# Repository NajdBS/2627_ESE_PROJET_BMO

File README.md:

# 2627_ESE_PROJET_BMO
# Robot BMO - Ramasseur de Canettes
Projet d'Option 3A ESE (2026-2027)

## Objectif

Concevoir un robot **entièrement autonome** qui ramasse des canettes rouges et vertes posées en vrac au centre d'un terrain, puis range chacune dans la zone de sa couleur, sans aucune intervention humaine.

## Mission du robot

1. Trouver une canette dans la zone centrale.
2. S'en approcher et la saisir.
3. Identifier sa couleur.
4. La déposer dans la bonne zone sans renverser les canettes déjà déposées.
5. Ressortir de la zone et revenir au centre.
6. Ne jamais reprendre une canette qui se trouve déjà dans une zone verte ou rouge.
7. Recommencer jusqu'à ce que la zone centrale soit vide, puis s'arrêter.
## Équipe
- Najd BEN SAAD
- Yassin GARAFI
- Achraf AHAL

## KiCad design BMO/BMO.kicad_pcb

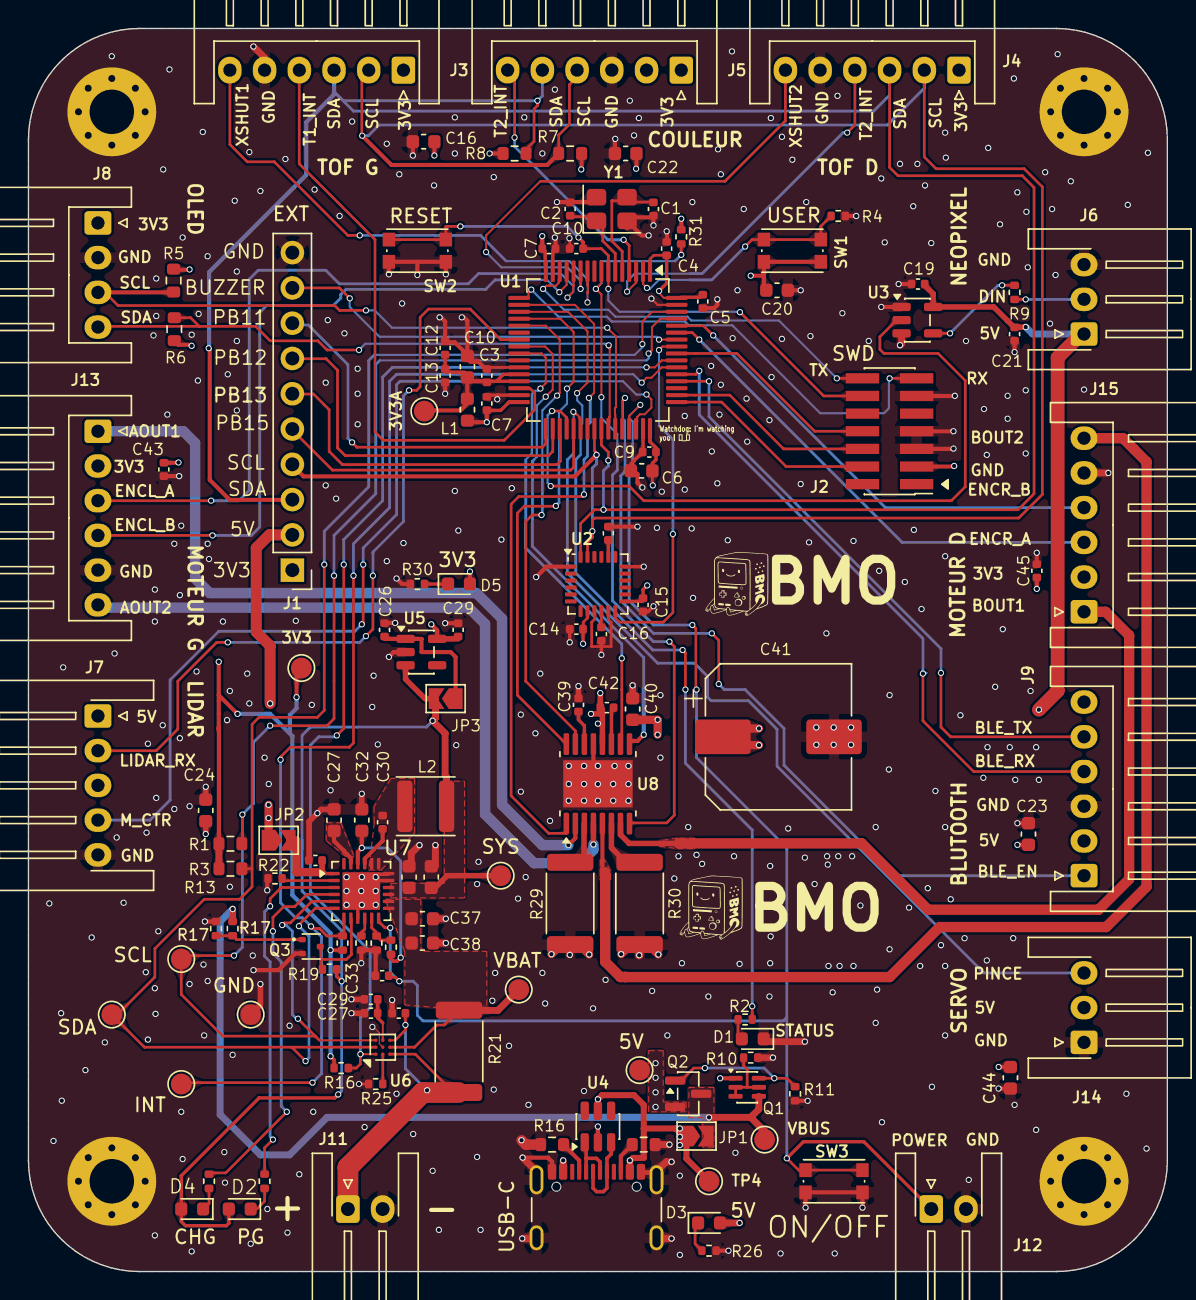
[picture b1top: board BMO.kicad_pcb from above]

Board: 4 copper layers, 82.0 x 89.5 mm, 131 parts (0 on the bottom side), 94 nets.

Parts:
3V3, 3V3A, 5V: TestPoint; TestPoint_Pad_D1.5mm
C1, C2: 10p; C_0402_1005Metric
C3, C4, C5, C7, C8, C9, C11, C15, C17, C19, C21, C34, C43, C45: 100n; C_0402_1005Metric
C6, C32: 4u7; C_0603_1608Metric
C10: 10n; C_0603_1608Metric
C12, C13, C25, C26, C30, C33: 1u; C_0402_1005Metric
C14, C42: 10n; C_0402_1005Metric
C16, C20, C22, C23, C24: 1u; C_0603_1608Metric
C18: 2n2/50V; C_0402_1005Metric
C27, C35, C36, C37, C38, C40, C44: 10u; C_0603_1608Metric
C28: 470n; C_0402_1005Metric
C29, C39: 2u2; C_0402_1005Metric
C31: 47n; C_0402_1005Metric
C41: 470u; CP_Elec_10x10
D1, D2: GREEN; LED_0603_1608Metric
D3: RED_5V; LED_0603_1608Metric
D4: ORANGE; LED_0603_1608Metric
D5: RED_3V; LED_0603_1608Metric
H1, H2, H3, H4: MountingHole_Pad; MountingHole_3.2mm_M3_Pad_Via
J1: EXT; PinHeader_1x10_P2.54mm_Vertical
J2: Conn_ST_STDC14; PinHeader_2x07_P1.27mm_Vertical_SMD
J3: TOF1_VL53L0X; JST_XH_S6B-XH-A_1x06_P2.50mm_Horizontal
J4: TOF2_VL53L0X; JST_XH_S6B-XH-A_1x06_P2.50mm_Horizontal
J5: COULEUR_I2C; JST_XH_S6B-XH-A_1x06_P2.50mm_Horizontal
J6: NEOPIXEL; JST_XH_S3B-XH-A-1_1x03_P2.50mm_Horizontal
J7: LIDAR_X2; JST_XH_S5B-XH-A-1_1x05_P2.50mm_Horizontal
J8: OLED_I2C; JST_XH_S4B-XH-A_1x04_P2.50mm_Horizontal
J9, J13, J15: Conn_01x06; JST_XH_S6B-XH-A_1x06_P2.50mm_Horizontal
J10: USB_C_Receptacle_USB2.0_16P; USB_C_Receptacle_GCT_USB4105-xx-A_16P_TopMnt_Horizontal
J11: BAT; JST_XH_S2B-XH-A-1_1x02_P2.50mm_Horizontal
J12: ON/OFF; JST_XH_S2B-XH-A-1_1x02_P2.50mm_Horizontal
J14: SERVO; JST_XH_S3B-XH-A-1_1x03_P2.50mm_Horizontal
JP1, JP2, JP3: SolderJumper_2_Open; SolderJumper-2_P1.3mm_Open_TrianglePad1.0x1.5mm
L1: 600R@100MHz; L_0603_1608Metric
L2: 1u; L_APV_ANR4020
Q1: MMDT2907A-7-F; SOT-363_SC-70-6
Q2: DMP1045U-7; SOT-23
Q3: DMN313DLT-7; SOT-523
R1, R3: 4k7; R_0603_1608Metric
R2, R26, R28: 1k; R_0402_1005Metric
R4, R16, R17, R19, R20, R22, R23, R24, R31: 10k; R_0402_1005Metric
R5, R6, R7, R8: 2k2; R_0603_1608Metric
R9: 330; R_0402_1005Metric
R10, R11: 100k; R_0402_1005Metric
R12: 4k7; R_0402_1005Metric
R13, R14: 5.1k; R_0603_1608Metric
R15: 100; R_0402_1005Metric
R18: 470; R_0402_1005Metric
R21: 10m; R_2512_6332Metric
R25, R27: 2k2; R_0402_1005Metric
R29, R30: 200m; R_2512_6332Metric
SW1: USER; SW_Push_1P1T_NO_CK_KMR2
SW2: SW_Push; SW_Push_1P1T_NO_CK_KMR2
SW3: nQON; SW_Push_1P1T_NO_CK_KMR2
SYS: TestPoint; TestPoint_Pad_D1.5mm
TP1, TP2, TP3, TP4, TP5: TestPoint; TestPoint_Pad_D1.5mm
U1: STM32G474RBTx; LQFP-64_10x10mm_P0.5mm
U2: MPU-6050; InvenSense_QFN-24_4x4mm_P0.5mm
U3: SN74AHCT1G125DBVR; SOT-23-5
U4: USBLC6-2SC6; SOT-23-6
U5: AP2112K-3.3; SOT-23-5
U6: BQ27220YZFR; Texas_DSBGA-9_1.62x1.58mm_Layout3x3_P0.5mm
U7: BQ25896RTW; Texas_RTW_WQFN-24-1EP_4x4mm_P0.5mm_EP2.7x2.7mm_ThermalVias
U8: DRV8833PWPR; HTSSOP-16-1EP_4.4x5mm_P0.65mm_EP3.4x5mm_Mask2.46x2.31mm_The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
VBAT: TestPoint; TestPoint_Pad_D1.5mm
VBUS: TestPoint; TestPoint_Pad_D1.5mm
Y1: 16MHz; Crystal_SMD_3225-4Pin_3.2x2.5mm

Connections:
+3.3V: 3V3.1 (1_1), C4.2, C5.2, C6.2, C7.2, C8.2, C9.2, C14.1, C15.1, C16.1, C20.1, C22.1, C30.1, C43.1, C45.1, D5.2 (A), J1.1, J2.3 (VCC), J3.1, J4.1, J5.1, J8.1, J13.2, J15.2, L1.1, R1.1, R3.1, R5.2, R6.2, R7.1, R8.1, R12.1, R16.2, R31.1, SW1.1, U1.1 (VBAT), U1.16 (VDD), U1.32 (VDD), U1.48 (VDD), U1.64 (VDD), U2.8 (VLOGIC), U2.13 (VDD), U5.5 (VOUT)
+5V: 5V.1 (1_1), C19.1, C21.2, C23.1, C24.1, C40.1, C41.1, C42.2, C44.1, D3.2 (A), J1.2, J6.1, J7.1, J9.2, J14.2, JP2.1 (A), Q1.1 (E1), Q2.2 (S), U3.5 (VCC), U8.12 (VM)
/Motors/ENC_L_A_TIM2_CH1: J13.3, U1.12 (PA0)
/Motors/ENC_L_B_TIM2_CH2: J13.4, U1.13 (PA1)
/Motors/ENC_R_A_TIM4_CH1: J15.3, U1.59 (PB6)
/Motors/ENC_R_B_TIM4_CH2: J15.4, U1.60 (PB7)
/Motors/MOT_L_IN1_TIM3_CH1: U1.20 (PA6), U8.16 (AIN1)
/Motors/MOT_L_IN2_TIM3_CH2: U1.21 (PA7), U8.15 (AIN2)
/Motors/MOT_R_IN1_TIM3_CH3: U1.24 (PB0), U8.9 (BIN1)
/Motors/MOT_R_IN2_TIM3_CH4: U1.25 (PB1), U8.10 (BIN2)
/Motors/SERVO_PINCE_TIM8_CH1: J14.3, U1.38 (PC6)
/Motors/VCP: C42.1, U8.11 (VCP)
/Motors/~FAULT: R31.2, U1.8 (PC0), U8.8 (~FAULT)
/Motors/~SLEEP: U1.18 (PA4), U8.1 (~SLEEP)
/Power/BAT: C37.1, C38.1, R21.1, U6.C2 (SRN), U7.13 (BAT), U7.14 (BAT), VBAT.1 (1_1)
/Power/CHARGER_INT: R12.2, TP3.1 (1_1), U1.54 (PC12), U7.7 (INT)
/Power/FG_GPOUT: R16.1, U1.55 (PD2), U6.A1 (GPOUT)
/Power/PWR_Bouton: C34.2, J12.1, SW3.1, U1.45 (PA11), U7.12 (~QON)
/Power/REGN: C32.1, R24.2, U7.22 (REGN)
/Power/STAT: R27.2, U7.4 (STAT)
/Power/USB_D+: J10.A6 (D+), J10.B6 (D+), U4.3 (I/O2)
/Power/USB_D-: J10.A7 (D-), J10.B7 (D-), U4.1 (I/O1)
/Power/~PG: R25.2, U7.3 (~PG)
/STM32G474RBT3/+3V3A: 3V3A.1 (1_1), C3.2, C10.2, C12.1, C13.1, L1.2, U1.28 (VREF+), U1.29 (VDDA)
/STM32G474RBT3/BLE_En: J9.1, U1.44 (PA10)
/STM32G474RBT3/BLE_USART3_RX: J9.4, U1.53 (PC11)
/STM32G474RBT3/BLE_USART3_TX: J9.5, U1.52 (PC10)
/STM32G474RBT3/BUZZER_TIM17_CH1: J1.9, U1.58 (PB5)
/STM32G474RBT3/COLOR_INT: J5.6, U1.4 (PC15)
/STM32G474RBT3/EXT_PB11: J1.8, U1.33 (PB11)
/STM32G474RBT3/EXT_PB12: J1.7, U1.34 (PB12)
/STM32G474RBT3/EXT_PB13: J1.6, U1.35 (PB13)
/STM32G474RBT3/EXT_PB15: J1.5, U1.37 (PB15)
/STM32G474RBT3/I2C1_SCL_Jauge: R1.2, TP2.1 (1_1), U1.61 (PB8), U6.A3 (SCL), U7.5 (SCL)
/STM32G474RBT3/I2C1_SDA_Jauge: R3.2, TP5.1 (1_1), U1.62 (PB9), U6.A2 (SDA), U7.6 (SDA)
/STM32G474RBT3/I2C2_SCL_OLED: J8.3, R5.1, U1.43 (PA9)
/STM32G474RBT3/I2C2_SDA_OLED: J8.4, R6.1, U1.42 (PA8)
/STM32G474RBT3/I2C3_SCL_ToF_TCS_MPU: J1.4, J3.2, J4.2, J5.4, R7.2, U1.40 (PC8), U2.23 (SCL)
/STM32G474RBT3/I2C3_SDA_ToF_TCS_MPU: J1.3, J3.3, J4.3, J5.5, R8.2, U1.41 (PC9), U2.24 (SDA)
/STM32G474RBT3/LED_STATUS: R2.1, U1.19 (PA5)
/STM32G474RBT3/LIDARX2__USART1_RX: J7.2, U1.23 (PC5)
/STM32G474RBT3/LIDAR_M_CTR_TIM16_CH1: J7.4, U1.46 (PA12)
/STM32G474RBT3/MPU_INT: U1.57 (PB4), U2.12 (INT)
/STM32G474RBT3/NEOPIXEL: U1.36 (PB14), U3.2
/STM32G474RBT3/NRST: C11.1, J2.12 (~RST), SW2.1, U1.7 (PG10)
/STM32G474RBT3/SWCLK: J2.6 (JCLK/SWCLK), U1.50 (PA14)
/STM32G474RBT3/SWDIO: J2.4 (JTMS/SWDIO), U1.49 (PA13)
/STM32G474RBT3/SWO: J2.8 (JTDO/SWO), U1.56 (PB3)
/STM32G474RBT3/TOF1_INT: J3.4, U1.30 (PB10)
/STM32G474RBT3/TOF2_INT: J4.4, U1.3 (PC14)
/STM32G474RBT3/USER_Bouton: R4.1, SW1.2, U1.2 (PC13)
/STM32G474RBT3/VCP_RX: J2.13 (VCP_RX), U1.17 (PA3)
/STM32G474RBT3/VCP_TX: J2.14 (VCP_TX), U1.14 (PA2)
/STM32G474RBT3/XSHUT_TOF1: J3.6, U1.10 (PC2)
/STM32G474RBT3/XSHUT_TOF2: J4.6, U1.11 (PC3)
/Sensors/DIN: J6.2, R9.2
/Sensors/NP_5V: R9.1, U3.4
AOUT1: J13.1, U8.2 (AOUT1)
AOUT2: J13.6, U8.4 (AOUT2)
BOUT1: J15.1, U8.7 (BOUT1)
BOUT2: J15.6, U8.5 (BOUT2)
GND: C1.2, C2.2, C3.1, C4.1, C5.1, C6.1, C7.1, C8.1, C9.1, C10.1, C11.2, C12.2, C13.2, C14.2, C15.2, C16.2, C17.2, C18.2, C19.2, C20.2, C21.1, C22.2, C23.2, C24.2, C25.2, C26.2, C27.2, C28.2, C29.2, C30.2, C32.2, C33.2, C34.1, C35.2, C36.2, C37.2, C38.2, C39.2, C40.2, C41.2, C43.2, C44.2, C45.2, D1.1 (K), H1.1 (1_1), H2.1 (1_1), H3.1 (1_1), H4.1 (1_1), J1.10, J2.5 (GND), J2.7 (GND), J2.11 (GNDDetect), J3.5, J4.5, J5.3, J6.3, J7.5, J8.2, J9.3, J10.A1 (GND), J10.A12 (GND), J10.B1 (GND), J10.B12 (GND), J10.SH (SHIELD), J11.2, J12.2, J13.5, J14.1, J15.5, Q3.2 (S), R4.2, R10.2, R11.2, R13.2, R14.2, R17.1, R18.2, R20.1, R22.2, R23.2, R26.2, R28.2, R29.1, R30.1, SW2.2, SW3.2, TP1.1 (1_1), U1.15 (VSS), U1.27 (VSSA), U1.31 (VSS), U1.47 (VSS), U1.63 (VSS), U2.1 (CLKIN), U2.9 (AD0), U2.11 (FSYNC), U2.18 (GND), U3.1, U3.3 (GND), U4.2 (GND), U5.2 (GND), U6.B2 (VSS), U7.9 (~CE), U7.17 (PGND), U7.18 (PGND), U7.25 (PAD), U8.13 (GND), U8.17 (GND), Y1.2 (G), Y1.4 (G)
unnamed: C31.2, L2.1, U7.19 (SW), U7.20 (SW)
unnamed: D1.2 (A), R2.2
unnamed: D2.1 (K), R25.1
unnamed: D3.1 (K), R26.1
unnamed: D4.1 (K), R27.1
unnamed: D5.1 (K), R28.1
unnamed: J10.A5 (CC1), R14.1
unnamed: J10.B5 (CC2), R13.1
unnamed: C33.1, J11.1, R21.2, U6.C1 (SRP), U6.C3 (BAT)
unnamed: J10.A4 (VBUS), J10.A9 (VBUS), J10.B4 (VBUS), J10.B9 (VBUS), JP1.1 (A), TP4.1 (1_1), U4.5 (VBUS)
unnamed: C25.1, JP2.2 (B), U7.1 (VBUS)
unnamed: C26.1, JP3.1 (A), U5.1 (VIN)
unnamed: Q1.2 (B1), Q1.3 (C2), Q1.5 (B2), R10.1
unnamed: Q1.6 (C1), Q2.1 (G), R11.1
unnamed: Q3.3 (D), R19.1, U7.8 (OTG)
unnamed: Q3.1 (G), R15.2, R17.2
unnamed: C1.1, U1.5 (PF0), Y1.3
unnamed: C2.1, U1.6 (PF1), Y1.1
unnamed: C18.1, U2.20 (CPOUT)
unnamed: C17.1, U2.10 (REGOUT)
unnamed: R23.1, U6.B1 (BIN)
unnamed: C28.1, C29.1, U6.B3 (VDD)
unnamed: C31.1, U7.21 (BTST)
unnamed: R18.1, U7.10 (ILIM)
unnamed: C27.1, U7.23 (PMID)
unnamed: R20.2, U7.2 (PSEL)
unnamed: R22.1, R24.1, U7.11 (TS)
unnamed: R29.2, U8.3 (AISEN)
unnamed: R30.2, U8.6 (BISEN)
unnamed: C39.1, U8.14 (VINT)
SYS: C35.1, C36.1, D2.2 (A), D4.2 (A), JP3.2 (B), L2.2, R19.2, SYS.1 (1_1), U5.3 (EN), U7.15 (SYS), U7.16 (SYS)
VBUS: JP1.2 (B), Q1.4 (E2), Q2.3 (D), R15.1, VBUS.1 (1_1)

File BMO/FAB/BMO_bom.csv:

Comment,Designator,Footprint,JLCPCB Part #
TestPoint,"3V3,3V3A1,5V1,SYS1,TP1,TP2,TP3,TP4,TP5,VBAT1,VBUS1",TestPoint:TestPoint_Pad_D1.5mm,
10p,"C1,C2",Capacitor_SMD:C_0402_1005Metric,C32949
100n,"C3,C4,C5,C7,C8,C9,C11,C15,C17,C19,C21,C34,C43,C45",Capacitor_SMD:C_0402_1005Metric,C1525
4u7,"C6,C32",Capacitor_SMD:C_0603_1608Metric,C19666
10n,C10,Capacitor_SMD:C_0603_1608Metric,C57112
1u,"C12,C13,C25,C26,C30,C33",Capacitor_SMD:C_0402_1005Metric,C52923
10n,"C14,C42",Capacitor_SMD:C_0402_1005Metric,C15195
1u,"C16,C20,C22,C23,C24",Capacitor_SMD:C_0603_1608Metric,C15849
2n2/50V,C18,Capacitor_SMD:C_0402_1005Metric,C77022
10u,"C27,C35,C36,C37,C38,C40,C44",Capacitor_SMD:C_0603_1608Metric,C96446
470n,C28,Capacitor_SMD:C_0402_1005Metric,C88946
2u2,"C29,C39",Capacitor_SMD:C_0402_1005Metric,C12530
47n,C31,Capacitor_SMD:C_0402_1005Metric,C77012
470u,C41,Capacitor_SMD:CP_Elec_10x10,C2165185
GREEN,"D1,D2",LED_SMD:LED_0603_1608Metric,C12624
RED_5V,D3,LED_SMD:LED_0603_1608Metric,C2286
ORANGE,D4,LED_SMD:LED_0603_1608Metric,C84269
RED_3V,D5,LED_SMD:LED_0603_1608Metric,C2286
EXT,J1,Connector_PinHeader_2.54mm:PinHeader_1x10_P2.54mm_Vertical,C492409
Conn_ST_STDC14,J2,Connector_PinHeader_1.27mm:PinHeader_2x07_P1.27mm_Vertical_SMD,C5307809
TOF1_VL53L0X,J3,Connector_JST:JST_XH_S6B-XH-A_1x06_P2.50mm_Horizontal,C157919
TOF2_VL53L0X,J4,Connector_JST:JST_XH_S6B-XH-A_1x06_P2.50mm_Horizontal,C157919
COULEUR_I2C,J5,Connector_JST:JST_XH_S6B-XH-A_1x06_P2.50mm_Horizontal,C157919
NEOPIXEL,J6,Connector_JST:JST_XH_S3B-XH-A-1_1x03_P2.50mm_Horizontal,C163036
LIDAR_X2,J7,Connector_JST:JST_XH_S5B-XH-A-1_1x05_P2.50mm_Horizontal,C163038
OLED_I2C,J8,Connector_JST:JST_XH_S4B-XH-A_1x04_P2.50mm_Horizontal,C157925
Conn_01x06,"J9,J13,J15",Connector_JST:JST_XH_S6B-XH-A_1x06_P2.50mm_Horizontal,C157919
USB_C_Receptacle_USB2.0_16P,J10,Connector_USB:USB_C_Receptacle_GCT_USB4105-xx-A_16P_TopMnt_Horizontal,C5184243
BAT,J11,Connector_JST:JST_XH_S2B-XH-A-1_1x02_P2.50mm_Horizontal,C163035
ON/OFF,J12,Connector_JST:JST_XH_S2B-XH-A-1_1x02_P2.50mm_Horizontal,C163035
SERVO,J14,Connector_JST:JST_XH_S3B-XH-A-1_1x03_P2.50mm_Horizontal,C163036
600R@100MHz,L1,Inductor_SMD:L_0603_1608Metric,C1002
1u,L2,Inductor_SMD:L_APV_ANR4020,C7497071
MMDT2907A-7-F,Q1,Package_TO_SOT_SMD:SOT-363_SC-70-6,C460232
DMP1045U-7,Q2,Package_TO_SOT_SMD:SOT-23,C177033
DMN313DLT-7,Q3,Package_TO_SOT_SMD:SOT-523,C155524
4k7,"R1,R3",Resistor_SMD:R_0603_1608Metric,C23162
1k,"R2,R26,R28",Resistor_SMD:R_0402_1005Metric,C11702
10k,"R4,R16,R17,R19,R20,R22,R23,R24,R31",Resistor_SMD:R_0402_1005Metric,C25744
2k2,"R5,R6",Resistor_SMD:R_0603_1608Metric,C4190
2k2,"R7,R8",Resistor_SMD:R_0603_1608Metric,C4190
330,R9,Resistor_SMD:R_0402_1005Metric,C25104
100k,"R10,R11",Resistor_SMD:R_0402_1005Metric,C25741
4k7,R12,Resistor_SMD:R_0402_1005Metric,C25900
5.1k,"R13,R14",Resistor_SMD:R_0603_1608Metric,C23186
100,R15,Resistor_SMD:R_0402_1005Metric,C25076
470,R18,Resistor_SMD:R_0402_1005Metric,C25117
10m,R21,Resistor_SMD:R_2512_6332Metric,C105366
2k2,"R25,R27",Resistor_SMD:R_0402_1005Metric,C25879
200m,"R29,R30",Resistor_SMD:R_2512_6332Metric,C83749
USER,SW1,Button_Switch_SMD:SW_Push_1P1T_NO_CK_KMR2,C72443
SW_Push,SW2,Button_Switch_SMD:SW_Push_1P1T_NO_CK_KMR2,C72443
nQON,SW3,Button_Switch_SMD:SW_Push_1P1T_NO_CK_KMR2,C72443
STM32G474RBTx,U1,Package_QFP:LQFP-64_10x10mm_P0.5mm,C1235414
MPU-6050,U2,Sensor_Motion:InvenSense_QFN-24_4x4mm_P0.5mm,C24112
SN74AHCT1G125DBVR,U3,Package_TO_SOT_SMD:SOT-23-5,C7484
USBLC6-2SC6,U4,Package_TO_SOT_SMD:SOT-23-6,C7519
AP2112K-3.3,U5,Package_TO_SOT_SMD:SOT-23-5,C51118
BQ27220YZFR,U6,Package_BGA:Texas_DSBGA-9_1.62x1.58mm_Layout3x3_P0.5mm,C528617
BQ25896RTW,U7,Package_DFN_QFN:Texas_RTW_WQFN-24-1EP_4x4mm_P0.5mm_EP2.7x2.7mm_ThermalVias,C181475
DRV8833PWPR,U8,Package_SO:HTSSOP-16-1EP_4.4x5mm_P0.65mm_EP3.4x5mm_Mask2.46x2.31mm_ThermalVias,C50506
16MHz,Y1,Crystal:Crystal_SMD_3225-4Pin_3.2x2.5mm,C13738

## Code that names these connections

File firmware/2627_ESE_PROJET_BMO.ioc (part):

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Mcu.Name=STM32G474R(B-C-E)Tx
Mcu.Package=LQFP64
Mcu.UserName=STM32G474RBTx
PA0.GPIOParameters=GPIO_PuPd,GPIO_Label
PA0.GPIO_Label=ENC_L_A
PA0.GPIO_PuPd=GPIO_PULLUP
PA0.Signal=S_TIM2_CH1
PA1.GPIOParameters=GPIO_PuPd,GPIO_Label
PA1.GPIO_Label=ENC_L_B
PA1.GPIO_PuPd=GPIO_PULLUP
PA1.Signal=S_TIM2_CH2
PA10.GPIOParameters=GPIO_Label
PA10.GPIO_Label=BLE_EN
PA10.Signal=GPIO_Output
PA11.GPIOParameters=GPIO_PuPd,GPIO_Label,GPIO_ModeDefaultEXTI
PA11.GPIO_Label=PWR_BUTTON
PA11.GPIO_ModeDefaultEXTI=GPIO_MODE_IT_FALLING
PA11.GPIO_PuPd=GPIO_PULLUP
PA11.Signal=GPXTI11
PA12.GPIOParameters=GPIO_Label
PA12.GPIO_Label=LIDAR_M_CTR
PA12.Signal=S_TIM16_CH1
PA13.Mode=Trace_Asynchronous_SW
PA13.Signal=SYS_JTMS-SWDIO
PA14.Mode=Trace_Asynchronous_SW
PA14.Signal=SYS_JTCK-SWCLK
PA2.GPIOParameters=GPIO_Label
PA2.GPIO_Label=VCP_TX
PA2.Mode=Asynchronous
PA2.Signal=USART2_TX
PA3.GPIOParameters=GPIO_Label
PA3.GPIO_Label=VCP_RX
PA3.Mode=Asynchronous
PA3.Signal=USART2_RX
PA4.GPIOParameters=GPIO_Label
PA4.GPIO_Label=MOT_nSLEEP
PA4.Signal=GPIO_Output
PA5.GPIOParameters=GPIO_Label
PA5.GPIO_Label=LED_STATUS
PA5.Signal=GPIO_Output
PA6.GPIOParameters=GPIO_Label
PA6.GPIO_Label=MOT_L_IN1
PA6.Signal=S_TIM3_CH1
PA7.GPIOParameters=GPIO_Label
PA7.GPIO_Label=MOT_L_IN2
PA7.Signal=S_TIM3_CH2
PA8.GPIOParameters=GPIO_Label,GPIO_Pu
PA8.GPIO_Label=OLED_SDA
PA8.GPIO_Pu=GPIO_PULLUP
PA8.Mode=I2C
PA8.Signal=I2C2_SDA
PA9.GPIOParameters=GPIO_Label,GPIO_Pu
PA9.GPIO_Label=OLED_SCL
PA9.GPIO_Pu=GPIO_PULLUP
PA9.Mode=I2C
PA9.Signal=I2C2_SCL
PB0.GPIOParameters=GPIO_Label
PB0.GPIO_Label=MOT_R_IN1
PB0.Signal=S_TIM3_CH3
PB1.GPIOParameters=GPIO_Label
PB1.GPIO_Label=MOT_R_IN2
PB1.Signal=S_TIM3_CH4
PB10.GPIOParameters=GPIO_PuPd,GPIO_Label,GPIO_ModeDefaultEXTI
PB10.GPIO_Label=INT_TOF_L
PB10.GPIO_ModeDefaultEXTI=GPIO_MODE_IT_FALLING
PB10.GPIO_PuPd=GPIO_PULLUP
PB10.Signal=GPXTI10
PB13.GPIOParameters=GPIO_Label
PB13.GPIO_Label=EXT_PB13 ( XSHUT_TOF_C )
PB13.Signal=GPIO_Output
PB14.GPIOParameters=GPIO_Label
PB14.GPIO_Label=NEOPIXEL
PB14.Signal=S_TIM15_CH1
PB3.Mode=Trace_Asynchronous_SW
PB3.Signal=SYS_JTDO-SWO
PB4.GPIOParameters=GPIO_PuPd,GPIO_Label,GPIO_ModeDefaultEXTI
PB4.GPIO_Label=MPU_INT
PB4.GPIO_ModeDefaultEXTI=GPIO_MODE_IT_RISING
PB4.GPIO_PuPd=GPIO_NOPULL
PB4.Signal=GPXTI4
PB5.GPIOParameters=GPIO_Label
PB5.GPIO_Label=BUZZER_PWM
PB5.Signal=S_TIM17_CH1
PB6.GPIOParameters=GPIO_PuPd,GPIO_Label
PB6.GPIO_Label=ENC_R_A
PB6.GPIO_PuPd=GPIO_PULLUP
PB6.Signal=S_TIM4_CH1
PB7.GPIOParameters=GPIO_PuPd,GPIO_Label
PB7.GPIO_Label=ENC_R_B
PB7.GPIO_PuPd=GPIO_PULLUP
PB7.Signal=S_TIM4_CH2
PB8-BOOT0.GPIOParameters=GPIO_Label
PB8-BOOT0.GPIO_Label=BAT_SCL
PB8-BOOT0.Mode=I2C
PB8-BOOT0.Signal=I2C1_SCL
PB9.GPIOParameters=GPIO_Label
PB9.GPIO_Label=BAT_SDA
PB9.Mode=I2C
PB9.Signal=I2C1_SDA
PC0.GPIOParameters=GPIO_PuPd,GPIO_Label,GPIO_ModeDefaultEXTI
PC0.GPIO_Label=MOT_nFAULT
PC0.GPIO_ModeDefaultEXTI=GPIO_MODE_IT_FALLING
PC0.GPIO_PuPd=GPIO_PULLUP
PC0.Signal=GPXTI0
PC10.GPIOParameters=GPIO_Label
PC10.GPIO_Label=BLE_TX
PC10.Mode=Asynchronous
PC10.Signal=USART3_TX
PC11.GPIOParameters=GPIO_Label
PC11.GPIO_Label=BLE_RX
PC11.Mode=Asynchronous
PC11.Signal=USART3_RX
PC12.GPIOParameters=GPIO_PuPd,GPIO_Label,GPIO_ModeDefaultEXTI
PC12.GPIO_Label=CHARGER_INT
PC12.GPIO_ModeDefaultEXTI=GPIO_MODE_IT_FALLING
PC12.GPIO_PuPd=GPIO_PULLUP
PC12.Signal=GPXTI12
PC13.GPIOParameters=GPIO_PuPd,GPIO_Label,GPIO_ModeDefaultEXTI
PC13.GPIO_Label=USER_BTN
PC13.GPIO_ModeDefaultEXTI=GPIO_MODE_IT_FALLING
PC13.GPIO_PuPd=GPIO_PULLUP
PC13.Signal=GPXTI13
PC14-OSC32_IN.GPIOParameters=GPIO_PuPd,GPIO_Label,GPIO_ModeDefaultEXTI
PC14-OSC32_IN.GPIO_Label=INT_TOF_R
PC14-OSC32_IN.GPIO_ModeDefaultEXTI=GPIO_MODE_IT_FALLING
PC14-OSC32_IN.GPIO_PuPd=GPIO_PULLUP
PC14-OSC32_IN.Signal=GPXTI14
PC15-OSC32_OUT.GPIOParameters=GPIO_PuPd,GPIO_Label,GPIO_ModeDefaultEXTI
PC15-OSC32_OUT.GPIO_Label=COLOR_INT
PC15-OSC32_OUT.GPIO_ModeDefaultEXTI=GPIO_MODE_IT_FALLING
PC15-OSC32_OUT.GPIO_PuPd=GPIO_PULLUP
PC15-OSC32_OUT.Signal=GPXTI15
PC2.GPIOParameters=GPIO_Label
PC2.GPIO_Label=XSHUT_TOF_L
PC2.Signal=GPIO_Output
PC3.GPIOParameters=GPIO_Label
PC3.GPIO_Label=XSHUT_TOF_R
PC3.Signal=GPIO_Output
PC4.GPIOParameters=GPIO_Label
PC4.GPIO_Label=LIDAR_TX_NC
PC4.Mode=Asynchronous
PC4.Signal=USART1_TX
PC5.GPIOParameters=GPIO_Label
PC5.GPIO_Label=LIDAR_RX
PC5.Mode=Asynchronous
PC5.Signal=USART1_RX
PC6.GPIOParameters=GPIO_Label
PC6.GPIO_Label=SERVO_PINCE
PC6.Signal=S_TIM8_CH1
PC8.GPIOParameters=GPIO_Label,GPIO_Pu
PC8.GPIO_Label=SENS_SCL
PC8.GPIO_Pu=GPIO_PULLUP
PC8.Mode=I2C
PC8.Signal=I2C3_SCL
PC9.GPIOParameters=GPIO_Label,GPIO_Pu
PC9.GPIO_Label=SENS_SDA
PC9.GPIO_Pu=GPIO_PULLUP
PC9.Mode=I2C
PC9.Signal=I2C3_SDA
PD2.GPIOParameters=GPIO_PuPd,GPIO_Label,GPIO_ModeDefaultEXTI
PD2.GPIO_Label=FG_GPOUT
PD2.GPIO_ModeDefaultEXTI=GPIO_MODE_IT_FALLING
PD2.GPIO_PuPd=GPIO_PULLUP
PD2.Signal=GPXTI2
PF0-OSC_IN.Mode=HSE-External-Oscillator
PF0-OSC_IN.Signal=RCC_OSC_IN
PF1-OSC_OUT.Mode=HSE-External-Oscillator
PF1-OSC_OUT.Signal=RCC_OSC_OUT
RCC.HSE_VALUE=8000000
RCC.SYSCLKFreq_VALUE=170000000
RCC.SYSCLKSource=RCC_SYSCLKSOURCE_PLLCLK
board=custom
